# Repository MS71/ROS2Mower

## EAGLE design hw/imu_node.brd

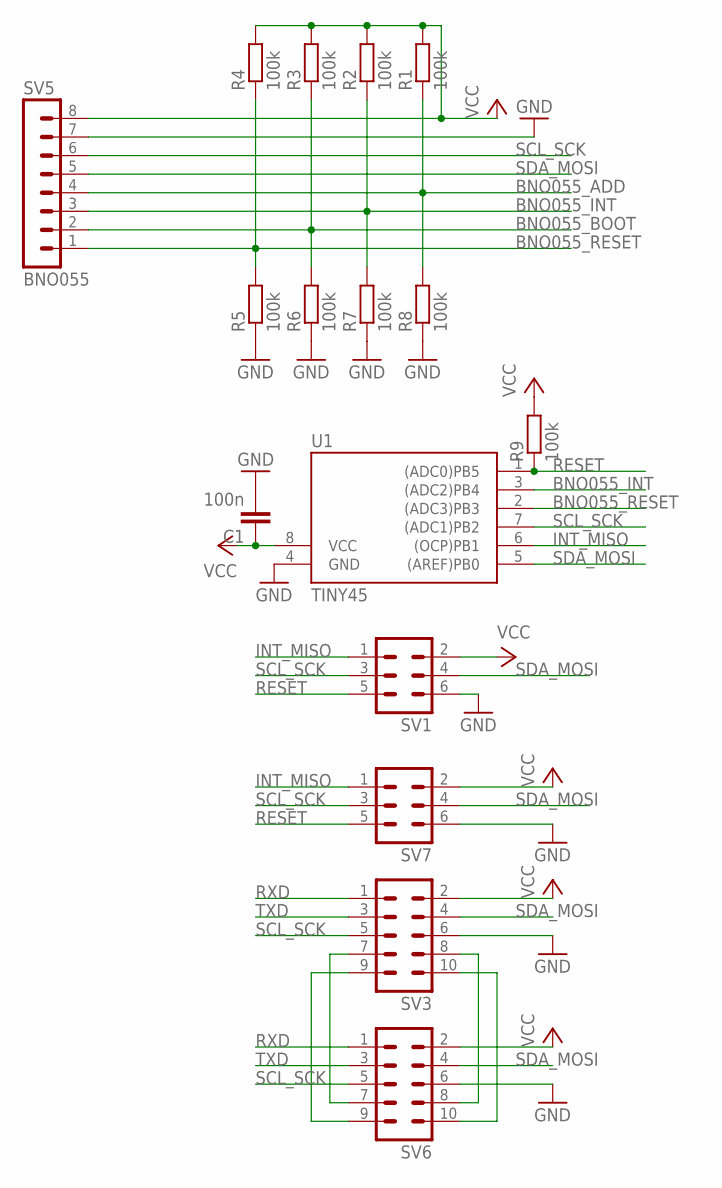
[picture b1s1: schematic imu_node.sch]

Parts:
C1: 100n; C0805
R1, R2, R3, R4, R5, R6, R7, R8, R9: 100k; M0805
SV1, SV7: ML6
SV3, SV6: ML10
SV5: BNO055; MA08-1
U1: TINY45; SOIC8

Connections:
BNO055_ADD: R1.1, R8.2, SV5.4
BNO055_BOOT: R3.1, R6.2, SV5.2
BNO055_INT: R2.1, R7.2, SV5.3, U1.3 ((ADC2)PB4)
BNO055_RESET: R4.1, R5.2, SV5.1, U1.2 ((ADC3)PB3)
GND: C1.2, R5.1, R6.1, R7.1, R8.1, SV1.6, SV3.6, SV5.7, SV6.6, SV7.6, U1.4 (GND)
INT_MISO: SV1.1, SV7.1, U1.6 ((OCP)PB1)
unnamed: SV3.7, SV6.7
unnamed: SV3.9, SV6.9
unnamed: SV3.8, SV6.8
unnamed: SV3.10, SV6.10
RESET: R9.1, SV1.5, SV7.5, U1.1 ((ADC0)PB5)
RXD: SV3.1, SV6.1
SCL_SCK: SV1.3, SV3.5, SV5.6, SV6.5, SV7.3, U1.7 ((ADC1)PB2)
SDA_MOSI: SV1.4, SV3.4, SV5.5, SV6.4, SV7.4, U1.5 ((AREF)PB0)
TXD: SV3.3, SV6.3
VCC: C1.1, R1.2, R2.2, R3.2, R4.2, R9.2, SV1.2, SV3.2, SV5.8, SV6.2, SV7.2, U1.8 (VCC)

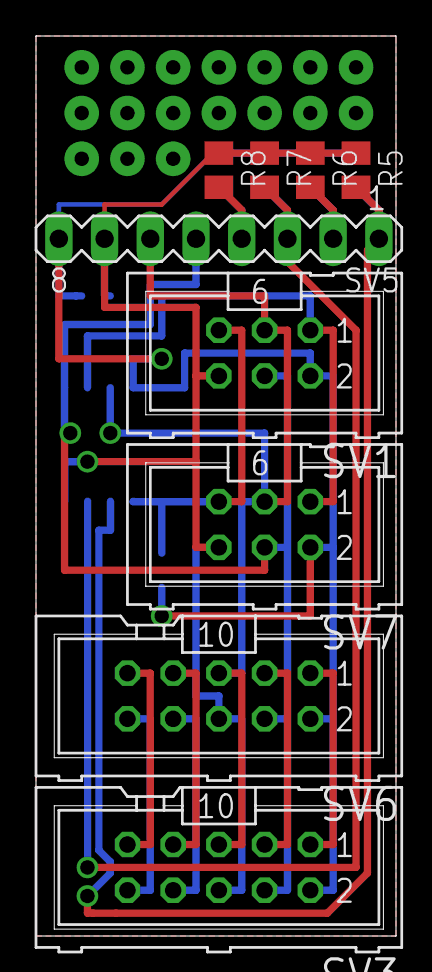
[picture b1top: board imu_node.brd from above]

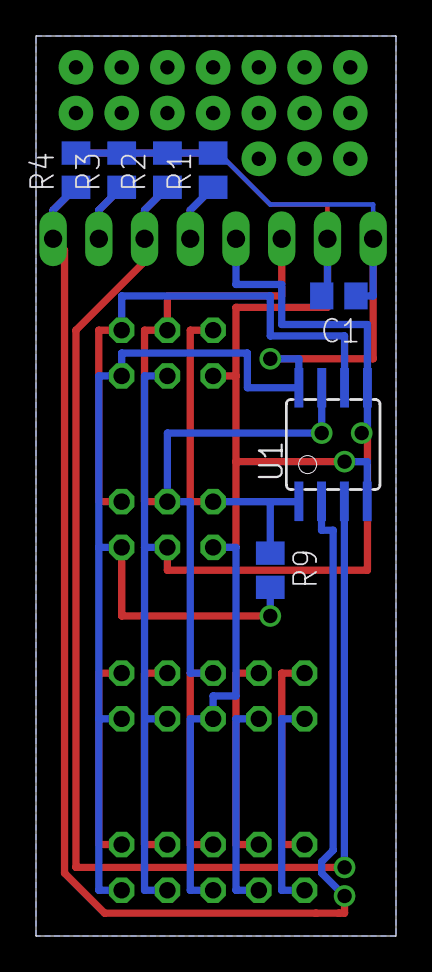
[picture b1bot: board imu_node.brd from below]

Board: 2 copper layers, 20.0 x 50.0 mm, 16 parts (7 on the bottom side), 16 nets.

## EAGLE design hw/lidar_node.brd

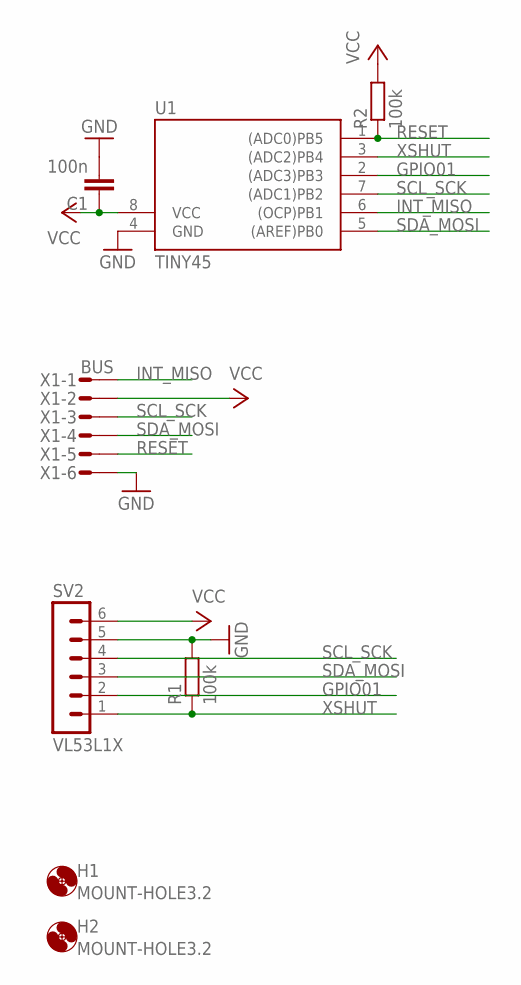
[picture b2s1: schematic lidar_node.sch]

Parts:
C1: 100n; C0805
H1, H2: MOUNT-HOLE3.2; 3,2
R1, R2: 100k; M0805
SV2: VL53L1X; MA06-1
U1: TINY45; SOIC8
X1: BUS; MICROMATCH-6

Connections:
GND: C1.2, R1.2, SV2.5, U1.4 (GND), X1.6
GPIO01: SV2.2, U1.2 ((ADC3)PB3)
INT_MISO: U1.6 ((OCP)PB1), X1.1
RESET: R2.1, U1.1 ((ADC0)PB5), X1.5
SCL_SCK: SV2.4, U1.7 ((ADC1)PB2), X1.3
SDA_MOSI: SV2.3, U1.5 ((AREF)PB0), X1.4
VCC: C1.1, R2.2, SV2.6, U1.8 (VCC), X1.2
XSHUT: R1.1, SV2.1, U1.3 ((ADC2)PB4)

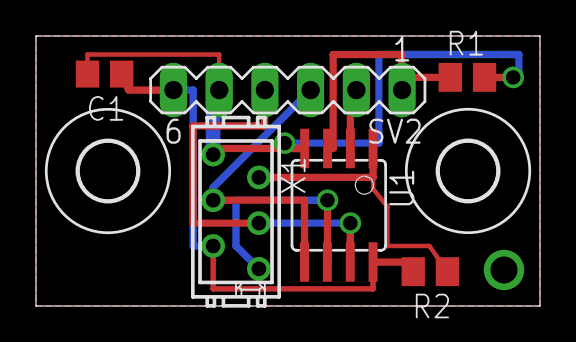
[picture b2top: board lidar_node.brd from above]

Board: 2 copper layers, 28.0 x 15.0 mm, 8 parts (0 on the bottom side), 8 nets.

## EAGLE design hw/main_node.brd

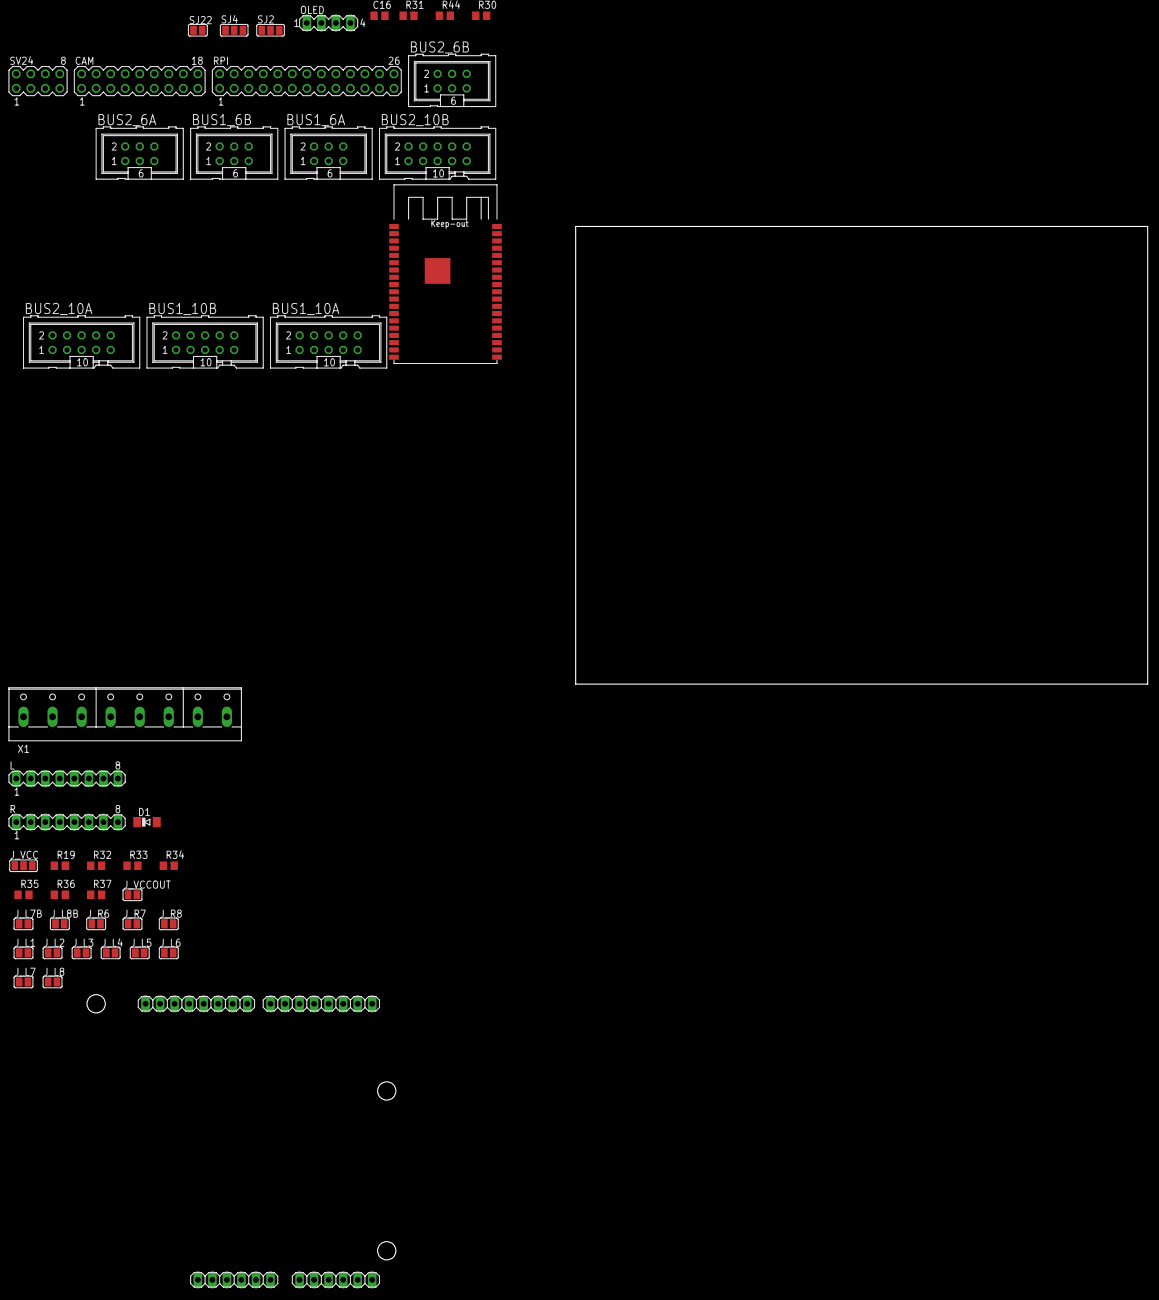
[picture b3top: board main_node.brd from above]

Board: 2 copper layers, 100.0 x 80.0 mm, 47 parts (0 on the bottom side), 61 nets, no tracks yet.

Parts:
BUS1_6A, BUS1_6B, BUS2_6A, BUS2_6B: ML6
BUS1_10A, BUS1_10B, BUS2_10A, BUS2_10B: ML10
C16: 0.1; C0805
CAM: MA09-2
D1: 4148; MINIMELF
IC2: ARDUINO2009_2
IC10: ESP32-WROVER
J_L1, J_L2, J_L3, J_L4, J_L5, J_L6, J_L7, J_L7B, J_L8, J_L8B: SJ
J_R6, J_R7, J_R8: SJ
J_VCC: SJ_2
J_VCCOUT: SJ
L: MA08-1
OLED: MA04-1
R: MA08-1
R19, R32, R33, R34, R35, R36, R37: R0805
R30, R44: 100k; R0805
R31: 470; R0805
RPI: MA13-2
SJ2, SJ4: SJ_2
SJ22: SJ
SV24: MA04-2
X1: W237-8P

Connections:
CAM_D0: CAM.16, IC10.IO5
CAM_D1: CAM.15, IC10.IO18
CAM_D2: CAM.14, IC10.IO19
CAM_D3: CAM.13, IC10.IO21
CAM_D4: CAM.12, IC10.SENSOR_VP
CAM_D5: CAM.11, IC10.SENSOR_VN
CAM_D6: CAM.10, IC10.IO34
CAM_D7: CAM.9, IC10.IO35
CAM_HSYNC: CAM.6, IC10.IO23
CAM_PCLK: CAM.7, IC10.IO22
CAM_RESET: CAM.17, IC10.IO32
CAM_SCL: CAM.3, IC10.IO27
CAM_SDA: CAM.4, IC10.IO26
CAM_VSYNC: CAM.5, IC10.IO25
ESP_AEN: C16.2, IC10.EN, R30.2, R31.1, SV24.6
ESP_BOOT: CAM.8, IC10.IO0, R44.1, SV24.4
ESP_RXD: IC10.RXD0, SV24.7
ESP_TXD: IC10.TXD0, SV24.2
ESP_U3.3: IC10.VDD33, R30.1, R44.2, SV24.8
FON1: BUS1_10A.3, BUS1_10B.3
FON2: BUS2_10A.3, BUS2_10B.3
GND: BUS1_6A.6, BUS1_6B.6, BUS1_10A.8, BUS1_10A.10, BUS1_10B.8, BUS1_10B.10, BUS2_6A.6, BUS2_6B.6, BUS2_10A.8, BUS2_10A.10, BUS2_10B.8, BUS2_10B.10, C16.1, IC2.4, IC2.5, IC2.27, IC10.GND, IC10.GND2, IC10.GND3, IC10.GND_2, R.1, RPI.6, RPI.9, RPI.20, RPI.25, SJ2.1, SJ4.1, SV24.1, X1.1, X1.2
INT1: BUS1_6A.1, BUS1_6B.1, BUS1_10A.9, BUS1_10B.9, RPI.7
INT2: BUS2_6A.1, BUS2_6B.1, BUS2_10A.9, BUS2_10B.9
LCD_1: OLED.1, SJ2.2
LCD_2: OLED.2, SJ4.2
unnamed: X1.7, X1.8
unnamed: X1.5, X1.6
unnamed: J_R6.1, R.6
unnamed: J_R7.1, R.7
unnamed: IC10.IO33, SJ22.2
unnamed: J_R8.1, R.8
unnamed: J_L7.2, J_L7B.2, L.7
unnamed: J_L6.2, L.6, R19.1
unnamed: J_L8.2, J_L8B.2, L.8
unnamed: J_L5.2, L.5, R34.1
unnamed: J_L4.2, L.4, R35.1
unnamed: J_L2.2, L.2, R37.1
unnamed: J_L3.2, L.3, R36.1
unnamed: J_L1.2, L.1
RESET1: BUS1_6A.5, BUS1_6B.5, BUS1_10A.5, BUS1_10B.5
RESET2: BUS2_6A.5, BUS2_6B.5, BUS2_10A.5, BUS2_10B.5
SCL1: BUS1_6A.3, BUS1_6B.3, BUS1_10A.7, BUS1_10B.7, RPI.5, SV24.3
SCL2: BUS2_6A.3, BUS2_6B.3, BUS2_10A.7, BUS2_10B.7, OLED.3
SDA1: BUS1_6A.4, BUS1_6B.4, BUS1_10A.1, BUS1_10B.1, RPI.3, SV24.5
SDA2: BUS2_6A.4, BUS2_6B.4, BUS2_10A.1, BUS2_10B.1, OLED.4
SPI_CS: RPI.22, SJ22.1
SPI_MISO: J_L2.1, RPI.21
SPI_MOSI: J_L3.1, RPI.19
U2_BUS: D1.A, J_L1.1, R32.1, R33.1
U3.3: RPI.1, RPI.17
U5: R.4, RPI.2, RPI.4
U33A: J_VCC.3, J_VCCOUT.2, R.2
U33B: J_VCC.1, R.3
U33_B1: BUS1_6A.2, BUS1_6B.2, BUS1_10A.2, BUS1_10B.2, BUS2_6A.2
U33_B2: BUS2_6B.2, BUS2_10A.2, BUS2_10B.2
U50_B1: BUS1_10A.4, BUS1_10B.4
U50_B2: BUS2_10A.4, BUS2_10B.4
UBATSW: BUS1_10A.6, BUS1_10B.6, BUS2_10A.6, BUS2_10B.6
U_OLED: SJ2.3, SJ4.3
VCC: J_VCC.2, R19.2, R32.2, R34.2, R35.2, R36.2, R37.2

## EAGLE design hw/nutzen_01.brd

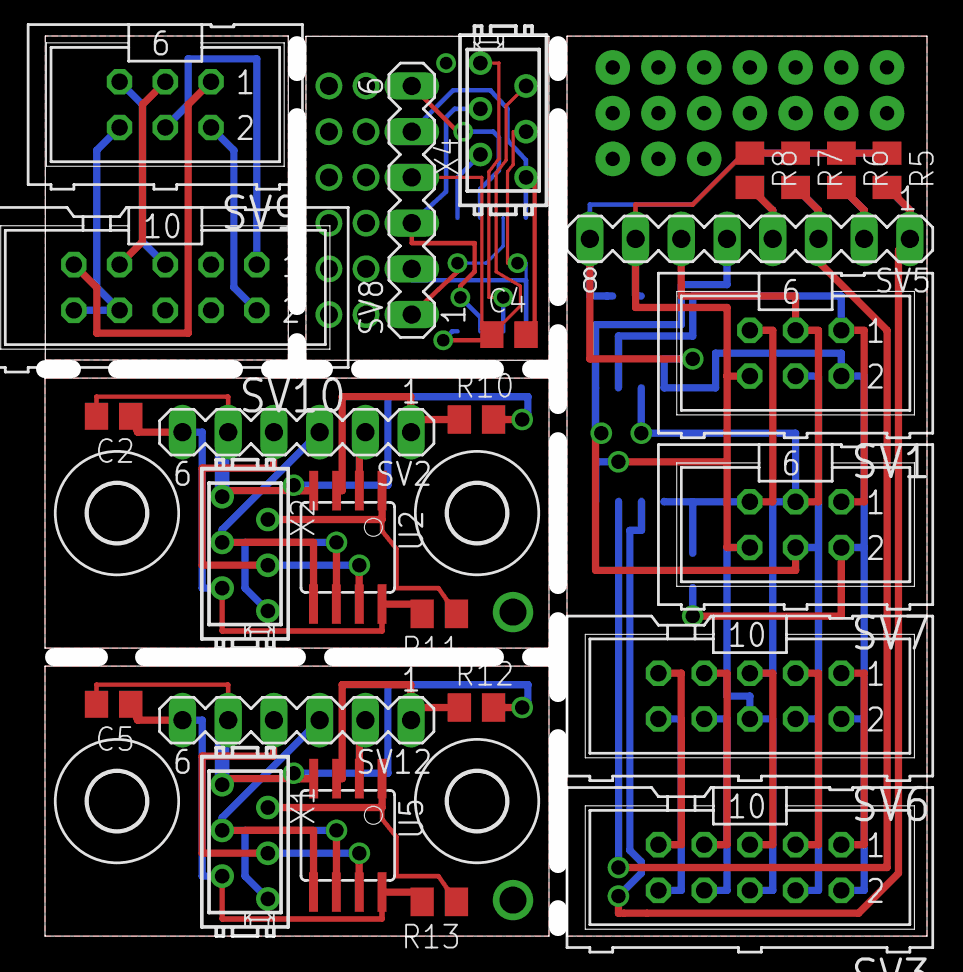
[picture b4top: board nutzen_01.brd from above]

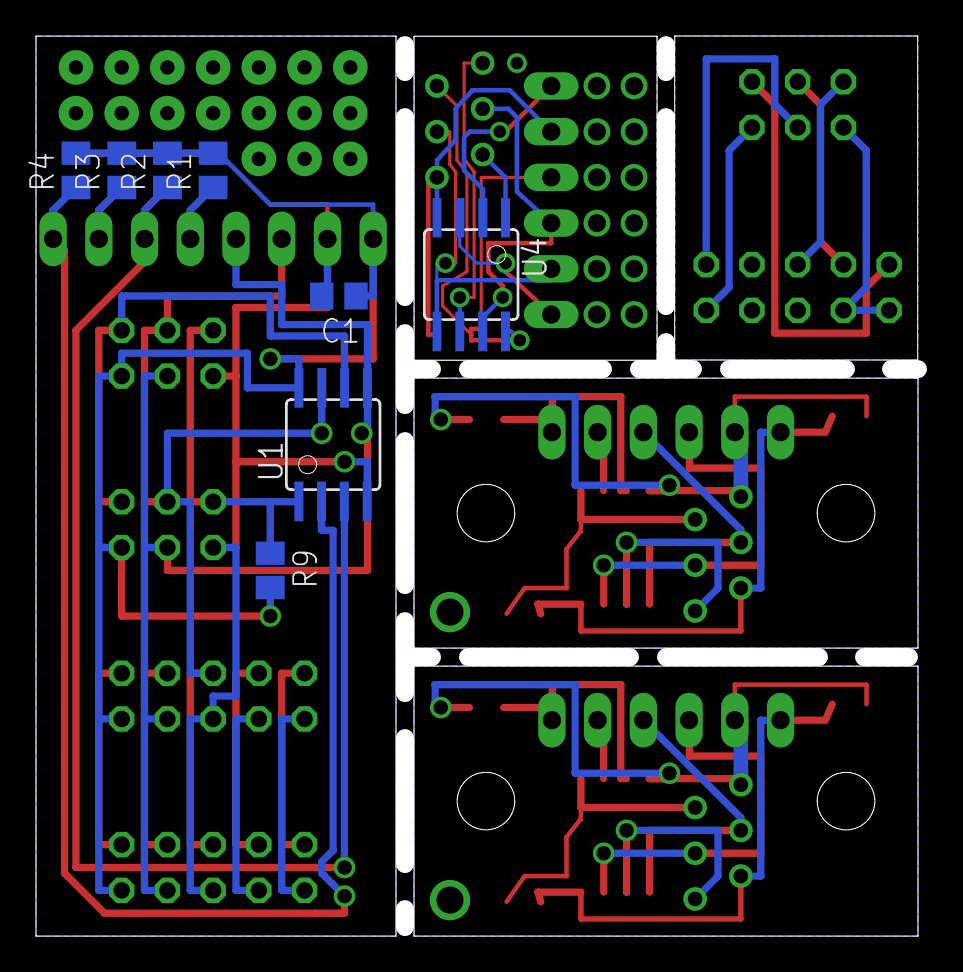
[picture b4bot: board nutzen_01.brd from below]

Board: 2 copper layers, 49.0 x 50.0 mm, 38 parts (8 on the bottom side), 46 nets.

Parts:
C1, C2, C4, C5: 100n; C0805
H1, H2, H11, H12: MOUNT-HOLE3.2; 3,2
R1, R2, R3, R4, R5, R6, R7, R8, R9, R10, R11, R12, R13: 100k; M0805
SV1, SV7, SV9: ML6
SV2, SV12: VL53L1X; MA06-1
SV3, SV6, SV10: ML10
SV5: BNO055; MA08-1
SV8: MA06-1
U1, U2, U4, U5: TINY45; SOIC8
X1, X2, X4: BUS; MICROMATCH-6

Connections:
BNO055_ADD: R1.1, R8.2, SV5.4
BNO055_BOOT: R3.1, R6.2, SV5.2
BNO055_INT: R2.1, R7.2, SV5.3, U1.3
BNO055_RESET: R4.1, R5.2, SV5.1, U1.2
GND: C1.2, R5.1, R6.1, R7.1, R8.1, SV1.6, SV3.6, SV5.7, SV6.6, SV7.6, U1.4
GND1: C2.2, R10.2, SV2.5, U2.4, X2.6
GND3: C4.2, SV8.5, U4.4, X4.6
GND4: C5.2, R12.2, SV12.5, U5.4, X1.6
GND5: SV9.6, SV10.8, SV10.10
GPIO01: SV2.2, U2.2
GPIO04: SV12.2, U5.2
INT: SV9.1, SV10.9
INT_MISO: SV1.1, SV7.1, U1.6
INT_MISO1: U2.6, X2.1
INT_MISO3: U4.6, X4.1
INT_MISO4: U5.6, X1.1
unnamed: SV3.7, SV6.7
unnamed: SV3.9, SV6.9
unnamed: SV3.8, SV6.8
unnamed: SV3.10, SV6.10
PB1: SV8.6, U4.2
PB2: SV8.1, U4.3
RESET: R9.1, SV1.5, SV7.5, U1.1
RESET1: R11.1, U2.1, X2.5
RESET3: U4.1, X4.5
RESET4: R13.1, U5.1, X1.5
RESET5: SV9.5, SV10.5
RXD: SV3.1, SV6.1
SCL: SV9.3, SV10.7
SCL_SCK: SV1.3, SV3.5, SV5.6, SV6.5, SV7.3, U1.7
SCL_SCK1: SV2.4, U2.7, X2.3
SCL_SCK3: SV8.3, U4.7, X4.3
SCL_SCK4: SV12.4, U5.7, X1.3
SDA: SV9.4, SV10.1
SDA_MOSI: SV1.4, SV3.4, SV5.5, SV6.4, SV7.4, U1.5
SDA_MOSI1: SV2.3, U2.5, X2.4
SDA_MOSI3: SV8.2, U4.5, X4.4
SDA_MOSI4: SV12.3, U5.5, X1.4
TXD: SV3.3, SV6.3
U33: SV9.2, SV10.2
VCC: C1.1, R1.2, R2.2, R3.2, R4.2, R9.2, SV1.2, SV3.2, SV5.8, SV6.2, SV7.2, U1.8
VCC1: C2.1, R11.2, SV2.6, U2.8, X2.2
VCC3: C4.1, SV8.4, U4.8, X4.2
VCC4: C5.1, R13.2, SV12.6, U5.8, X1.2
XSHUT1: R10.1, SV2.1, U2.3
XSHUT3: R12.1, SV12.1, U5.3

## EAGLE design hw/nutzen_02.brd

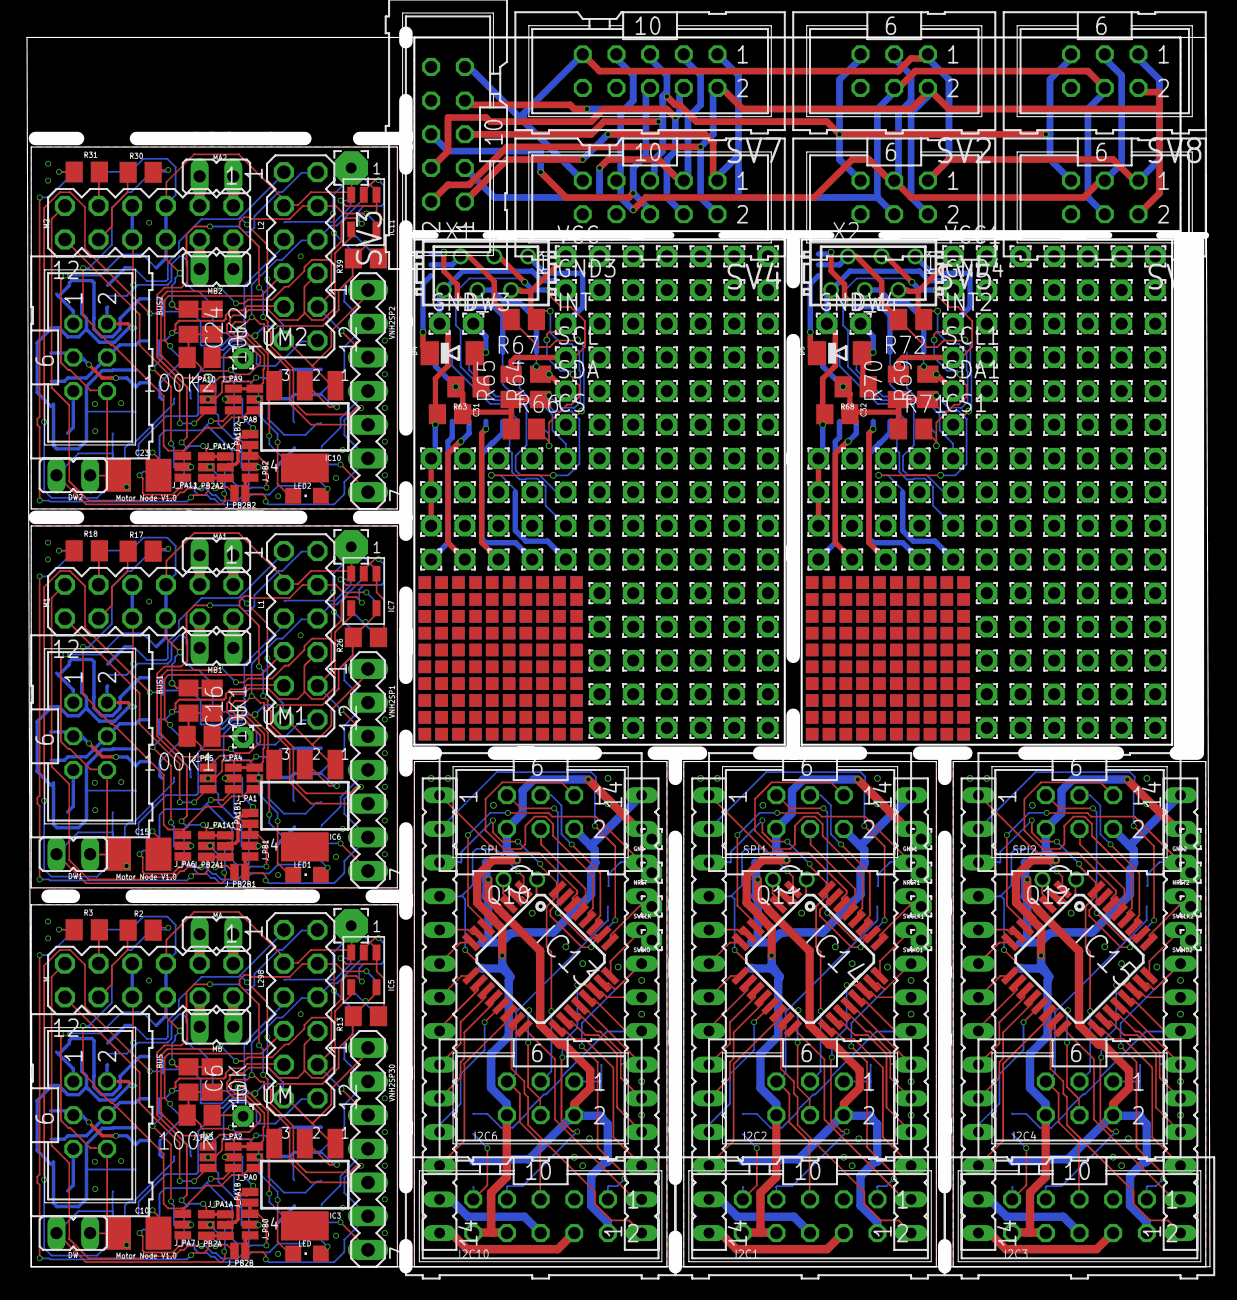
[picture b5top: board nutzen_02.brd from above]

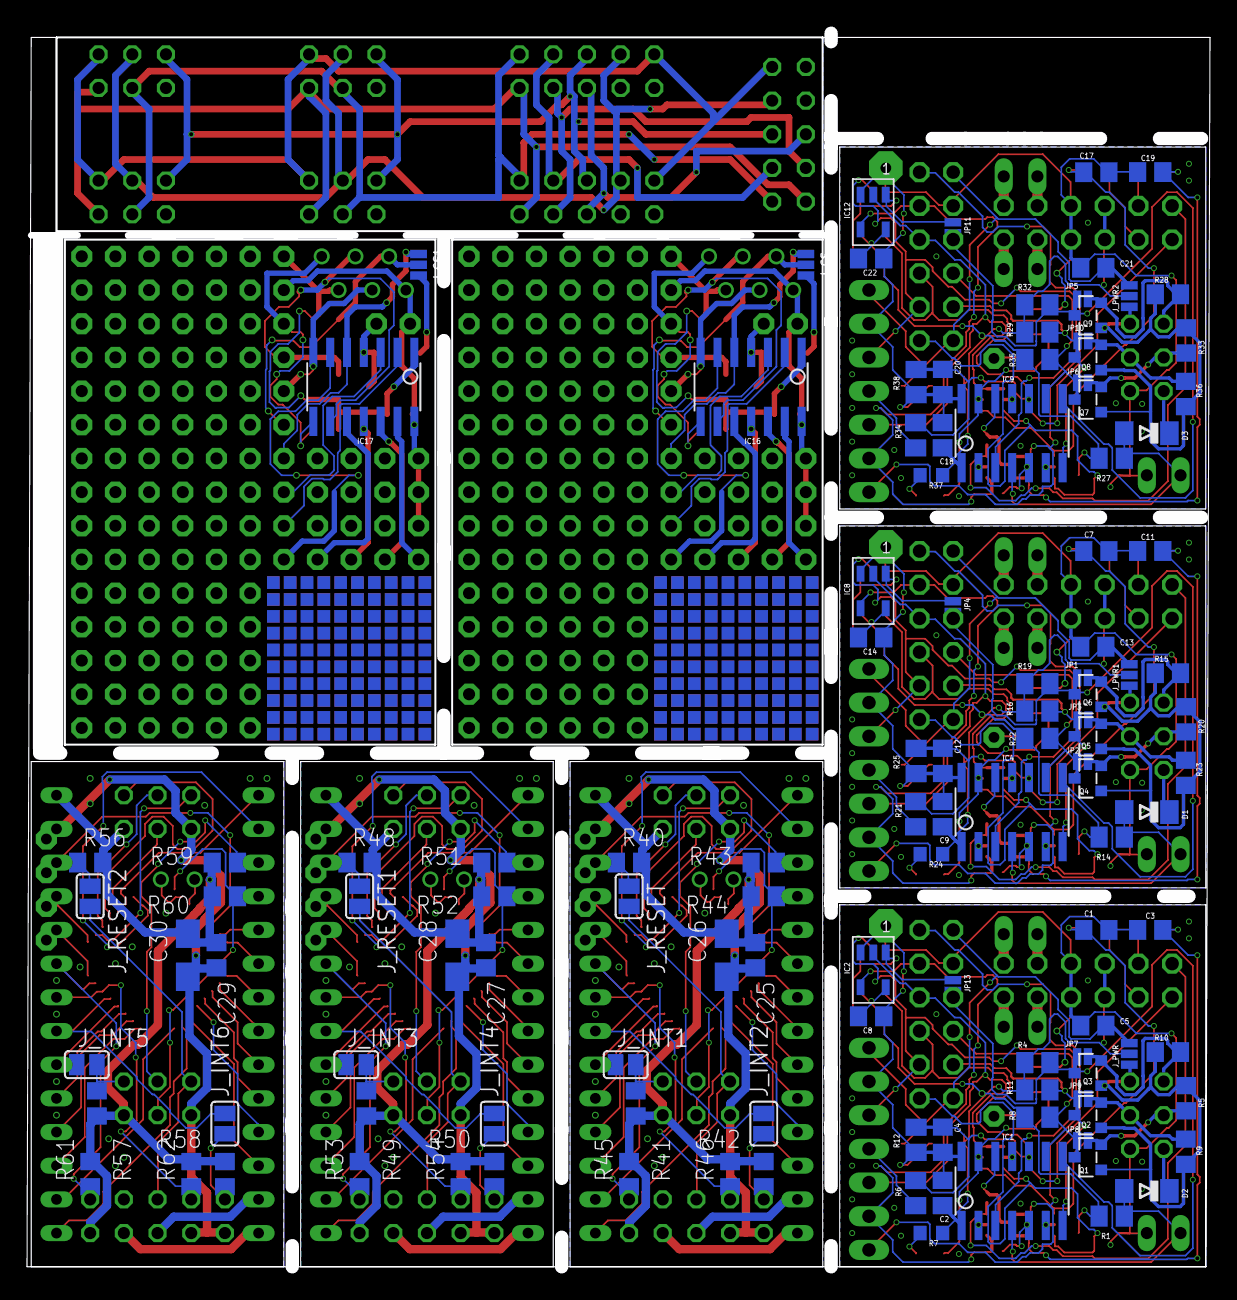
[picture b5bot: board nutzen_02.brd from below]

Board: 2 copper layers, 89.2 x 92.7 mm, 497 parts (121 on the bottom side), 269 nets.

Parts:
10K, 10K1, 10K2, 100K, 100K1, 100K2: 10k; M0805
BUS, BUS1, BUS2: ML6
C1, C3, C7, C11, C17, C19: 1n; C0805
C2, C4, C6, C9, C12, C16, C18, C20, C24, C31, C32: 100n; C0805
C5, C8, C13, C14, C21, C22: 0.1; C0805
C10, C15, C23: 100uF/6V; B/3528-21R
C25, C27, C29: C0805
C26, C28, C30: B/3528-21W
CS, CS1: 1,6/0,9
D1, D2, D3, D4, D5: MINIMELF
DW, DW1, DW2: JP1
DW3, DW4: 1,6/0,9
GND, GND1, GND2: 1,6/0,8
GND3, GND4: 1,6/0,9
GND_, GND_1: 1,6/0,9
I2C1, I2C3, I2C10: ML10
I2C2, I2C4, I2C6: ML6
IC1, IC4, IC9, IC16, IC17: TINY84 or TINY841; SOIC14
IC2, IC5, IC7, IC8, IC11, IC12: SOT-23/5
IC3, IC6, IC10: MCP1703DB; SOT223
IC13, IC14, IC15: STM32G071; LQFP-32
INT, INT0, INT1, INT2: 1,6/0,9
JP1, JP2, JP3, JP5, JP6, JP7, JP8, JP9, JP10: SMT-JUMPER_2_NC_PASTE_NO-SILK
JP4, JP11, JP13: SMT-JUMPER_2_NO_NO-SILK
J_CS, J_CS1: SMT-JUMPER_3_1-NC_PASTE_NO-SILK
J_INT1, J_INT2, J_INT3, J_INT4, J_INT5, J_INT6: SJ
J_PA0, J_PA1, J_PA1A, J_PA1A1, J_PA1A2, J_PA2, J_PA3, J_PA4, J_PA5, J_PA6, J_PA7, J_PA8, J_PA9, J_PA10, J_PA11: SMT-JUMPER_3_1-NC_PASTE_NO-SILK
J_PA1B, J_PA1B1, J_PA1B2: SMT-JUMPER_2_NO_NO-SILK
J_PB0, J_PB1, J_PB2, J_PB2A, J_PB2A1, J_PB2A2: SMT-JUMPER_3_1-NC_PASTE_NO-SILK
J_PB2B, J_PB2B1, J_PB2B2: SMT-JUMPER_2_NO_NO-SILK
J_PWR, J_PWR1, J_PWR2: SMT-JUMPER_3_1-NC_PASTE_NO-SILK
J_RESET, J_RESET1, J_RESET2: SJ
L, L3, L4: FE14
L1, L2, L298: MA06-2
LED, LED1, LED2: CHIPLED_0805
M, M1, M2: MA06-2
MA, MA1, MA2: JP1
MB, MB1, MB2: JP1
NRST, NRST1, NRST2: 1,6/0,8
PA0, PA1, PA2, PA3, PA4, PA5, PA6, PA7, PA8, PA9: 1,6/0,9
PAD1, PAD2, PAD3: 2,54/0,8
PAD4, PAD5, PAD6, PAD7, PAD8, PAD9, PAD10, PAD11, PAD12, PAD13, PAD14, PAD15, PAD16, PAD17, PAD18, PAD19, PAD20, PAD21, PAD22, PAD23, PAD24, PAD25, PAD26, PAD27, PAD28, PAD29, PAD30, PAD31, PAD32, PAD33, PAD34, PAD35, PAD36, PAD37, PAD38, PAD39, PAD40, PAD41, PAD42, PAD43, PAD44, PAD45, PAD46, PAD47, PAD48, PAD49, PAD50, PAD51, PAD52, PAD53, PAD54, PAD55, PAD56, PAD57, PAD58, PAD59, PAD60, PAD61, PAD62, PAD63, PAD64, PAD65, PAD66, PAD67, PAD68, PAD69, PAD70, PAD71, PAD72, PAD73, PAD74, PAD75, PAD76, PAD77, PAD78, PAD79, PAD80, PAD81, PAD82, PAD83, PAD84, PAD85, PAD86, PAD87, PAD88, PAD89, PAD90, PAD91, PAD92, PAD93, PAD94, PAD95, PAD96, PAD97, PAD98, PAD99, PAD100, PAD101, PAD102, PAD103, PAD104, PAD105, PAD106, PAD107, PAD108, PAD109, PAD110, PAD111, PAD112, PAD113, PAD114, PAD115, PAD116, PAD117, PAD118, PAD119, PAD120, PAD121, PAD122, PAD123, PAD124, PAD125, PAD126, PAD127, PAD128, PAD129, PAD130, PAD131, PAD132, PAD133, PAD134, PAD135, PAD136, PAD137, PAD138, PAD139, PAD140, PAD141, PAD142, PAD143, PAD144, PAD145, PAD146, PAD147, PAD148, PAD149, PAD150, PAD151, PAD152, PAD153, PAD154, PAD155, PAD156, PAD157, PAD158, PAD159, PAD160, PAD161, PAD162, PAD163, PAD164, PAD165, PAD166, PAD167, PAD168, PAD169, PAD170, PAD171, PAD172, PAD173, PAD174, PAD175, PAD176, PAD177, PAD178, PAD179, PAD180, PAD181, PAD182, PAD183, PAD184, PAD185, PAD186, PAD187, PAD188, PAD189, PAD190, PAD191, PAD192, PAD193, PAD194, PAD195, PAD196, PAD197, PAD198, PAD199, PAD200, PAD201, PAD202, PAD203, PAD204, PAD205, PAD206, PAD207: 1,6/0,9
PB0, PB1, PB2, PB3: 1,6/0,9
P_UM, P_UM1, P_UM2: 1,6/0,8
Q1, Q2, Q3, Q4, Q5, Q6, Q7, Q8, Q9: BSS138; SOT23
Q10, Q11, Q12: TC26V
R, R47, R55: FE14
R1, R4, R6, R8, R11, R12, R14, R16, R19, R21, R22, R25, R27, R29, R32, R34, R35, R38, R63, R64, R65, R66, R67, R68, R69, R70, R71, R72: 10k; M0805
R2, R3, R17, R18, R30, R31: 1k; M0805
R5, R9, R10, R13, R15, R20, R23, R26, R28, R33, R36, R39: 10k; R0805
R7, R24, R37: 1k; R0603
R40, R41, R42, R43, R44, R45, R46, R48, R49, R50, R51, R52, R53, R54, R56, R57, R58, R59, R60, R61, R62: R0805
SCL, SCL1: 1,6/0,9
SDA, SDA1: 1,6/0,9
SPI, SPI1, SPI2: ML6
SV1, SV2, SV5, SV8: ML6
SV3, SV4, SV7: ML10
SWCLK, SWCLK1, SWCLK2: 1,6/0,8
SWDIO, SWDIO1, SWDIO2: 1,6/0,8
VCC, VCC1: 1,6/0,9
VNH2SP1, VNH2SP2, VNH2SP30: MA07-1
X1, X2: BUS; MICROMATCH-6

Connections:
BUS_INT: BUS.1, JP7.1, Q3.2, R10.2
BUS_INT1: BUS1.1, JP1.1, Q6.2, R15.2
BUS_INT2: BUS2.1, JP5.1, Q9.2, R28.2
BUS_INT3: IC16.8, INT.1, R66.2, X1.1
BUS_INT4: IC17.8, INT2.1, R71.2, X2.1
BUS_P1: CS1.1, J_CS1.2, R72.2, X2.5
BUS_P5: CS.1, J_CS.2, R67.2, X1.5
BUS_RESET: BUS.5, D2.C
BUS_RESET1: BUS1.5, D1.C
BUS_RESET2: BUS2.5, D3.C
BUS_RESET3: I2C6.5, I2C10.5, J_RESET.1
BUS_RESET4: I2C1.5, I2C2.5, J_RESET1.1
BUS_RESET5: I2C3.5, I2C4.5, J_RESET2.1
BUS_RESET6: D4.C, J_CS.3
BUS_RESET7: D5.C, J_CS1.3
BUS_SCL: BUS.3, JP8.1, Q1.2, R5.2
BUS_SCL1: BUS1.3, JP2.1, Q4.2, R20.2
BUS_SCL2: BUS2.3, JP6.1, Q7.2, R33.2
BUS_SCL3: IC16.9, R65.2, SCL.1, X1.3
BUS_SCL4: IC17.9, R70.2, SCL1.1, X2.3
BUS_SDA: BUS.4, JP9.1, Q2.2, R9.2
BUS_SDA1: BUS1.4, JP3.1, Q5.2, R23.2
BUS_SDA2: BUS2.4, JP10.1, Q8.2, R36.2
BUS_SDA3: IC16.7, R64.2, SDA.1, X1.4
BUS_SDA4: IC17.7, R69.2, SDA1.1, X2.4
DEBUGWIRE: D2.A, DW.1, IC1.4, R1.2
DEBUGWIRE1: D1.A, DW1.1, IC4.4, R14.2
DEBUGWIRE2: D3.A, DW2.1, IC9.4, R27.2
DW: D4.A, DW3.1, IC16.4, R63.2
DW1: D5.A, DW4.1, IC17.4, R68.2
FON: SV3.3, SV4.3, SV7.3
GND: 10K.1, BUS.6, C1.1, C2.2, C3.2, C4.1, C5.2, C6.1, C8.2, C10.-, DW.2, IC1.14, IC2.3, IC3.2, IC5.3, L298.3, M.5, M.6, PAD1.1, R12.1, VNH2SP30.2
GND1: 10K1.1, BUS1.6, C7.1, C9.2, C11.2, C12.1, C13.2, C14.2, C15.-, C16.1, DW1.2, IC4.14, IC6.2, IC7.3, IC8.3, L1.3, M1.5, M1.6, PAD2.1, R25.1, VNH2SP1.2
GND2: 10K2.1, BUS2.6, C17.1, C18.2, C19.2, C20.1, C21.2, C22.2, C23.-, C24.1, DW2.2, IC9.14, IC10.2, IC11.3, IC12.3, L2.3, M2.5, M2.6, PAD3.1, R38.1, VNH2SP2.2
GND3: C25.2, C26.-, GND.1, I2C6.6, I2C10.8, I2C10.10, IC13.5, R.13, SPI.6
GND4: C27.2, C28.-, GND1.1, I2C1.8, I2C1.10, I2C2.6, IC14.5, R47.13, SPI1.6
GND5: C29.2, C30.-, GND2.1, I2C3.8, I2C3.10, I2C4.6, IC15.5, R55.13, SPI2.6
GND6: C31.2, GND3.1, GND_.1, IC16.14, PAD103.1, PAD104.1, PAD105.1, X1.6
GND7: C32.2, GND4.1, GND_1.1, IC17.14, PAD205.1, PAD206.1, PAD207.1, X2.6
GND8: SV1.6, SV2.6, SV3.8, SV3.10, SV4.8, SV4.10, SV5.6, SV7.8, SV7.10, SV8.6
INT: SV1.1, SV2.1, SV3.9, SV4.9, SV5.1, SV7.9, SV8.1
INT0: IC16.5, INT0.1, J_CS.1
INT1: I2C6.1, J_INT1.1, R41.1
INT2: I2C10.9, J_INT2.1, R42.1
INT3: I2C2.1, J_INT3.1, R49.1
INT4: I2C1.9, J_INT4.1, R50.1
INT5: I2C4.1, J_INT5.1, R57.1
INT6: I2C3.9, J_INT6.1, R58.1
INT7: IC17.5, INT1.1, J_CS1.1
INT_MISO: IC1.8, JP7.2, JP13.1, L298.5, Q3.3, R4.1
INT_MISO1: IC4.8, JP1.2, JP4.1, L1.5, Q6.3, R19.1
INT_MISO2: IC9.8, JP5.2, JP11.1, L2.5, Q9.3, R32.1
MA_A: IC2.2, J_PA0.1, J_PA2.3, L298.6, VNH2SP30.5
MA_A1: IC8.2, J_PA1.1, J_PA4.3, L1.6, VNH2SP1.5
MA_A2: IC12.2, J_PA8.1, J_PA9.3, L2.6, VNH2SP2.5
MA_B: IC2.4, J_PB0.3, J_PB2B.1, L298.4, VNH2SP30.6
MA_B1: IC8.4, J_PB1.3, J_PB2B1.1, L1.4, VNH2SP1.6
MA_B2: IC12.4, J_PB2.3, J_PB2B2.1, L2.4, VNH2SP2.6
MA_CS: R6.1, VNH2SP30.4
MA_CS1: R21.1, VNH2SP1.4
MA_CS2: R34.1, VNH2SP2.4
MA_CS_: C4.2, IC1.10, J_PA3.2, R6.2, R12.2
MA_CS_1: C12.2, IC4.10, J_PA5.2, R21.2, R25.2
MA_CS_2: C20.2, IC9.10, J_PA10.2, R34.2, R38.2
MA_E1: M.9, R3.2
MA_E1_: C3.1, J_PA1A.3, J_PB2A.1, R3.1
MA_E1_1: C11.1, J_PA1A1.3, J_PB2A1.1, R18.1
MA_E1_2: C19.1, J_PA1A2.3, J_PB2A2.1, R31.1
MA_E2: J_PA1B.2, J_PB0.1, M.11
MA_E3: M1.9, R18.2
MA_E4: J_PA1B1.2, J_PB1.1, M1.11
MA_E5: M2.9, R31.2
MA_E6: J_PA1B2.2, J_PB2.1, M2.11
MA_EN__MB_A: IC1.3, IC5.2, L298.10, VNH2SP30.3
MA_EN__MB_A1: IC4.3, IC7.2, L1.10, VNH2SP1.3
MA_EN__MB_A2: IC9.3, IC11.2, L2.10, VNH2SP2.3
MA_N: M.3, MA.1
MA_N1: M1.3, MA1.1
MA_N2: M2.3, MA2.1
MA_P: M.1, MA.2
MA_P1: M1.1, MA1.2
MA_P2: M2.1, MA2.2
MA_PWM: J_PA1A.1, J_PB2A.3, L298.2, VNH2SP30.7
MA_PWM1: J_PA1A1.1, J_PB2A1.3, L1.2, VNH2SP1.7
MA_PWM2: J_PA1A2.1, J_PB2A2.3, L2.2, VNH2SP2.7
MB_B: IC5.4, J_PA3.3, L298.8
MB_B1: IC7.4, J_PA5.3, L1.8
MB_B2: IC11.4, J_PA10.3, L2.8
MB_E1: M.10, R2.2
MB_E1_: C1.2, J_PA0.3, J_PA7.1, R2.1
MB_E1_1: C7.2, J_PA1.3, J_PA6.1, R17.1
MB_E1_2: C17.2, J_PA8.3, J_PA11.1, R30.1
MB_E2: J_PA3.1, M.12
MB_E3: J_PA5.1, M1.12
MB_E4: M1.10, R17.2
MB_E5: J_PA10.1, M2.12
MB_E6: M2.10, R30.2
MB_N: M.4, MB.2
MB_N1: M1.4, MB1.2
MB_N2: M2.4, MB2.2
MB_P: M.2, MB.1
MB_P1: M1.2, MB1.1
MB_P2: M2.2, MB2.1
MB_PWM: J_PA2.1, J_PA7.3, L298.12
MB_PWM1: J_PA4.1, J_PA6.3, L1.12
MB_PWM2: J_PA9.1, J_PA11.3, L2.12
unnamed: LED1.A, R24.1
unnamed: 100K.1, P_UM.1
unnamed: IC7.1, IC8.1, JP4.2, R26.1
unnamed: IC2.1, IC5.1, JP13.2, R13.1
unnamed: 100K1.1, P_UM1.1
unnamed: LED.A, R7.1
unnamed: LED2.A, R37.1
unnamed: IC11.1, IC12.1, JP11.2, R39.1
unnamed: 100K2.1, P_UM2.1
unnamed: IC14.2, Q11.2
unnamed: IC14.3, Q11.1
unnamed: IC15.2, Q12.2
unnamed: IC15.3, Q12.1
unnamed: IC13.2, Q10.2
unnamed: IC13.3, Q10.1
NRST: IC13.6, J_RESET.2, NRST.1, R.12, R40.1
NRST1: IC14.6, J_RESET1.2, NRST1.1, R47.12, R48.1
NRST2: IC15.6, J_RESET2.2, NRST2.1, R55.12, R56.1
PA0: 10K.2, 100K.2, C6.2, IC1.13, J_PA0.2, LED.C
PA1: IC1.12, J_PA1A.2, J_PA1B.1
PA2: IC1.11, J_PA2.2
PA3: 10K1.2, 100K1.2, C16.2, IC4.13, J_PA1.2, LED1.C
PA4: IC4.12, J_PA1A1.2, J_PA1B1.1
PA5: IC4.11, J_PA4.2
PA6: IC4.6, J_PA6.2
PA7: IC1.6, J_PA7.2
PA8: 10K2.2, 100K2.2, C24.2, IC9.13, J_PA8.2, LED2.C
PA9: IC9.12, J_PA1A2.2, J_PA1B2.1
PA10: IC9.11, J_PA9.2
PA11: IC9.6, J_PA11.2
PA12: IC13.7, L.5
PA13: IC13.8, L.6
PA14: IC13.9, L.7
PA15: IC13.10, L.8
PA16: IC13.11, L.9
PA17: IC13.12, L.10
PA18: IC13.18, R.4
PA19: IC13.19, R.5
PA20: IC13.13, L.11
PA21: IC13.14, L.12
PA22: IC13.21, J_INT2.2, R.7
PA23: IC14.7, L3.5
PA24: IC14.8, L3.6
PA25: IC14.9, L3.7
PA26: IC14.10, L3.8
PA27: IC14.11, L3.9
PA28: IC14.12, L3.10
PA29: IC14.18, R47.4
PA30: IC14.19, R47.5
PA31: IC14.13, L3.11
PA32: IC14.14, L3.12
PA33: IC14.21, J_INT4.2, R47.7
PA34: IC15.7, L4.5
PA35: IC15.8, L4.6
PA36: IC15.9, L4.7
PA37: IC15.10, L4.8
PA38: IC15.11, L4.9
PA39: IC15.12, L4.10
PA40: IC15.18, R55.4
PA41: IC15.19, R55.5
PA42: IC15.13, L4.11
PA43: IC15.14, L4.12
PA44: IC15.21, J_INT6.2, R55.7
PA45: IC16.13, PA0.1
PA46: IC16.6, PA7.1
PA47: IC16.10, PA3.1
PA48: IC16.11, PA2.1
PA49: IC16.12, PA1.1
PA50: IC17.13, PA4.1
PA51: IC17.6, PA9.1
PA52: IC17.10, PA8.1
PA53: IC17.11, PA6.1
PA54: IC17.12, PA5.1
PB0: IC1.2, J_PB0.2
PB1: IC4.2, J_PB1.2
PB2: IC1.5, J_PB2A.2, J_PB2B.2
PB3: IC4.5, J_PB2A1.2, J_PB2B1.2
PB4: IC9.2, J_PB2.2
PB5: IC9.5, J_PB2A2.2, J_PB2B2.2
PB6: IC13.16, R.2
PB7: IC13.30, L.1
PB8: IC13.15, R.1
PB9: IC13.31, L.2
PB10: IC14.16, R47.2
PB11: IC14.17, R47.3
PB12: IC14.30, L3.1
PB13: IC14.15, R47.1
PB14: IC14.31, L3.2
PB15: IC13.17, R.3
PB16: IC15.16, R55.2
PB17: IC15.17, R55.3
PB18: IC15.30, L4.1
PB19: IC15.15, R55.1
PB20: IC15.31, L4.2
PB21: IC16.3, PB1.1
PB22: IC16.2, PB0.1
PB23: IC17.3, PB3.1
PB24: IC17.2, PB2.1
PC1: IC14.20, J_INT3.2, R47.6
PC2: IC15.20, J_INT5.2, R55.6
PC6: IC13.20, J_INT1.2, R.6
RESET: SV1.5, SV2.5, SV3.5, SV4.5, SV5.5, SV7.5, SV8.5
SCL: SV1.3, SV2.3, SV3.7, SV4.7, SV5.3, SV7.7, SV8.3
SCL1: I2C6.3, IC13.32, L.3, R43.1
SCL2: I2C10.7, IC13.22, R.8, R46.1
SCL3: I2C2.3, IC14.32, L3.3, R51.1
SCL4: I2C1.7, IC14.22, R47.8, R54.1
SCL5: I2C4.3, IC15.32, L4.3, R59.1
SCL6: I2C3.7, IC15.22, R55.8, R62.1
SCL_SCK: IC1.9, JP8.2, L298.7, Q1.3, R8.1
SCL_SCK1: IC4.9, JP2.2, L1.7, Q4.3, R22.1
SCL_SCK2: IC9.9, JP6.2, L2.7, Q7.3, R35.1
SDA: SV1.4, SV2.4, SV3.1, SV4.1, SV5.4, SV7.1, SV8.4
SDA1: I2C6.4, IC13.1, L.4, R44.1
SDA2: I2C10.1, IC13.23, R.9, R45.1
SDA3: I2C2.4, IC14.1, L3.4, R52.1
SDA4: I2C1.1, IC14.23, R47.9, R53.1
SDA5: I2C4.4, IC15.1, L4.4, R60.1
SDA6: I2C3.1, IC15.23, R55.9, R61.1
SDA_MOSI: IC1.7, JP9.2, L298.9, Q2.3, R11.1
SDA_MOSI1: IC4.7, JP3.2, L1.9, Q5.3, R16.1
SDA_MOSI2: IC9.7, JP10.2, L2.9, Q8.3, R29.1
SPI1_MISO: IC13.28, SPI.1
SPI1_MISO1: IC14.28, SPI1.1
SPI1_MISO2: IC15.28, SPI2.1
SPI1_MOSI: IC13.29, SPI.4
SPI1_MOSI1: IC14.29, SPI1.4
SPI1_MOSI2: IC15.29, SPI2.4
SPI1_SCK: IC13.27, SPI.3
SPI1_SCK1: IC14.27, SPI1.3
SPI1_SCK2: IC15.27, SPI2.3
SPI1_SS: IC13.26, SPI.5
SPI1_SS1: IC14.26, SPI1.5
SPI1_SS2: IC15.26, SPI2.5
SWCLK: IC13.25, R.11, SWCLK.1
SWCLK1: IC14.25, R47.11, SWCLK1.1
SWCLK2: IC15.25, R55.11, SWCLK2.1
SWDIO: IC13.24, R.10, SWDIO.1
SWDIO1: IC14.24, R47.10, SWDIO1.1
SWDIO2: IC15.24, R55.10, SWDIO2.1
U1: C13.1, IC6.1, J_PWR1.1, L1.1, L1.11, VNH2SP1.1
U2: C21.1, IC10.1, J_PWR2.1, L2.1, L2.11, VNH2SP2.1
U3: I2C10.4, L.14
U4: I2C1.4, L3.14
U5: C5.1, IC3.1, J_PWR.1, L298.1, L298.11, VNH2SP30.1
U6: I2C3.4, L4.14
U14: SV3.4, SV4.4, SV7.4
U14SW: SV3.6, SV4.6, SV7.6
U33: SV1.2, SV2.2, SV3.2, SV4.2, SV5.2, SV7.2, SV8.2
UBAT: I2C10.6, L.13
UBAT1: I2C1.6, L3.13
UBAT2: I2C3.6, L4.13
U_BUS: BUS.2, J_PWR.3, Q1.1, Q2.1, Q3.1, R5.1, R9.1, R10.1
U_BUS1: BUS1.2, J_PWR1.3, Q4.1, Q5.1, Q6.1, R15.1, R20.1, R23.1
U_BUS2: BUS2.2, J_PWR2.3, Q7.1, Q8.1, Q9.1, R28.1, R33.1, R36.1
VCC: C2.1, C8.1, C10.+, IC1.1, IC2.5, IC3.3, IC5.5, J_PWR.2, M.7, M.8, R1.1, R4.2, R7.2, R8.2, R11.2, R13.2
VCC1: C9.1, C14.1, C15.+, IC4.1, IC6.3, IC7.5, IC8.5, J_PWR1.2, M1.7, M1.8, R14.1, R16.2, R19.2, R22.2, R24.2, R26.2
VCC2: C18.1, C22.1, C23.+, IC9.1, IC10.3, IC11.5, IC12.5, J_PWR2.2, M2.7, M2.8, R27.1, R29.2, R32.2, R35.2, R37.2, R39.2
VCC3: C25.1, C26.+, I2C6.2, I2C10.2, IC13.4, R.14, R40.2, R41.2, R42.2, R43.2, R44.2, R45.2, R46.2, SPI.2
VCC4: C27.1, C28.+, I2C1.2, I2C2.2, IC14.4, R47.14, R48.2, R49.2, R50.2, R51.2, R52.2, R53.2, R54.2, SPI1.2
VCC5: C29.1, C30.+, I2C3.2, I2C4.2, IC15.4, R55.14, R56.2, R57.2, R58.2, R59.2, R60.2, R61.2, R62.2, SPI2.2
VCC6: C31.1, IC16.1, R63.1, R64.1, R65.1, R66.1, R67.1, VCC.1, X1.2
VCC7: C32.1, IC17.1, R68.1, R69.1, R70.1, R71.1, R72.1, VCC1.1, X2.2

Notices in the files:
parts and their libraries:
SparkFun-Jumpers: Licensing: Creative Commons ShareAlike 4.0 International - https://creativecommons.org/licenses/by-sa/4.0
